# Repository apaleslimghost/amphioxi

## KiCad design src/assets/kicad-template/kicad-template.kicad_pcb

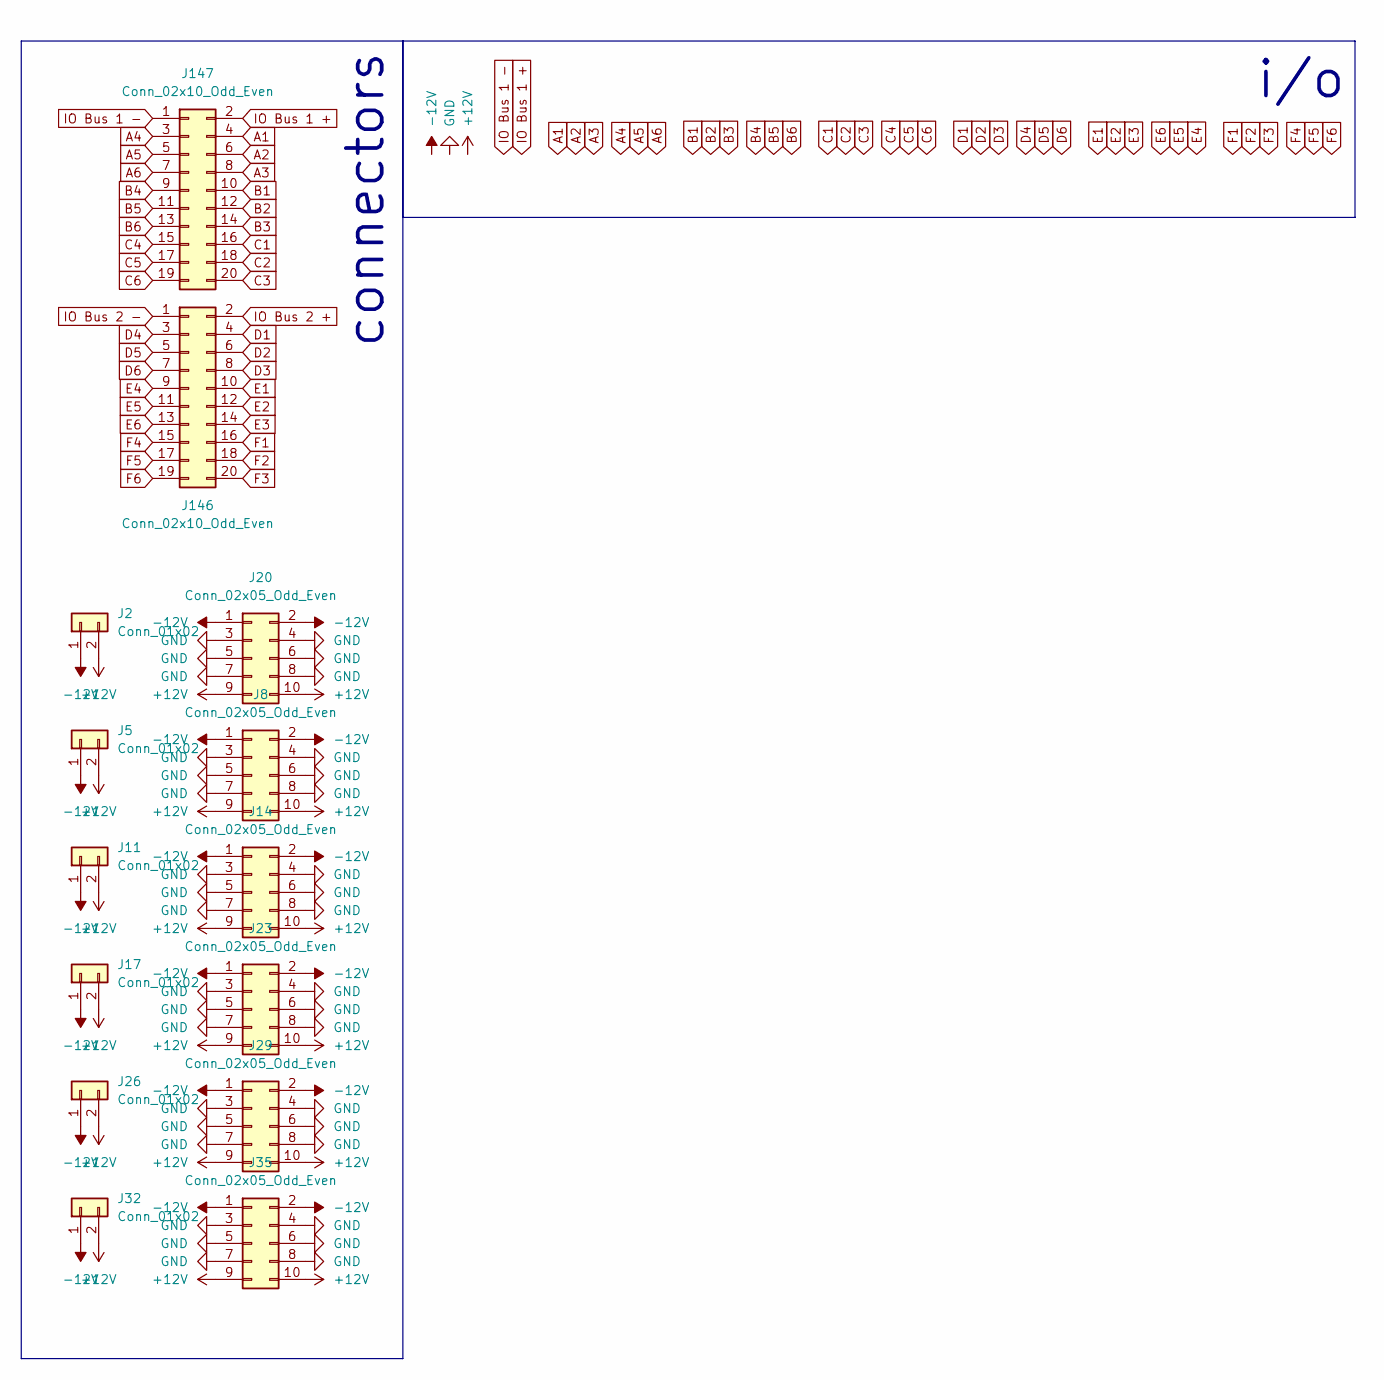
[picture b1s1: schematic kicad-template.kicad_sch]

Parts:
J2, J5, J11, J17, J26, J32: Conn_01x02; PinHeader_1x02_P2.54mm_Vertical_StripboardEuroPower
J8, J14, J20, J23, J29, J35: Conn_02x05_Odd_Even; PinHeader_2x05_P2.54mm_Vertical_StripboardEuroPower
J146, J147: Conn_02x10_Odd_Even; PinHeader_2x10_P2.00mm_Vertical

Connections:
+12V: J2.2, J5.2, J8.9, J8.10, J11.2, J14.9, J14.10, J17.2, J20.9, J20.10, J23.9, J23.10, J26.2, J29.9, J29.10, J32.2, J35.9, J35.10
-12V: J2.1, J5.1, J8.1, J8.2, J11.1, J14.1, J14.2, J17.1, J20.1, J20.2, J23.1, J23.2, J26.1, J29.1, J29.2, J32.1, J35.1, J35.2
A1: J147.4
A2: J147.6
A3: J147.8
A4: J147.3
A5: J147.5
A6: J147.7
B1: J147.10
B2: J147.12
B3: J147.14
B4: J147.9
B5: J147.11
B6: J147.13
C1: J147.16
C2: J147.18
C3: J147.20
C4: J147.15
C5: J147.17
C6: J147.19
D1: J146.4
D2: J146.6
D3: J146.8
D4: J146.3
D5: J146.5
D6: J146.7
E1: J146.10
E2: J146.12
E3: J146.14
E4: J146.9
E5: J146.11
E6: J146.13
F1: J146.16
F2: J146.18
F3: J146.20
F4: J146.15
F5: J146.17
F6: J146.19
GND: J8.3, J8.4, J8.5, J8.6, J8.7, J8.8, J14.3, J14.4, J14.5, J14.6, J14.7, J14.8, J20.3, J20.4, J20.5, J20.6, J20.7, J20.8, J23.3, J23.4, J23.5, J23.6, J23.7, J23.8, J29.3, J29.4, J29.5, J29.6, J29.7, J29.8, J35.3, J35.4, J35.5, J35.6, J35.7, J35.8
IO Bus 1 +: J147.2
IO Bus 1 -: J147.1
IO Bus 2 +: J146.2
IO Bus 2 -: J146.1

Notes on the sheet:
i/o
connectors

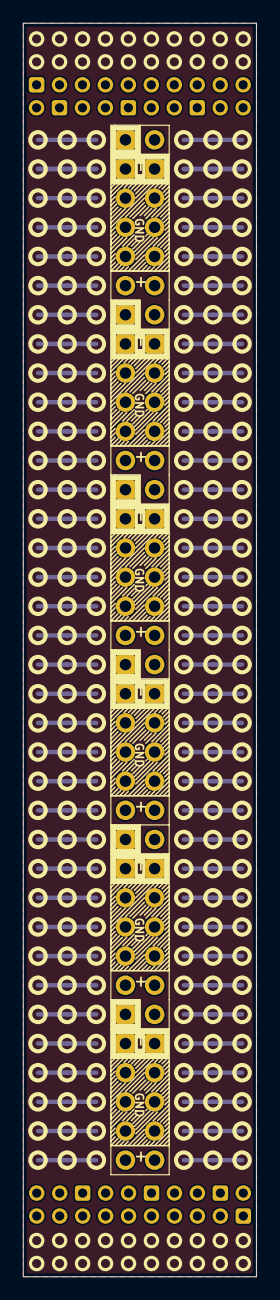
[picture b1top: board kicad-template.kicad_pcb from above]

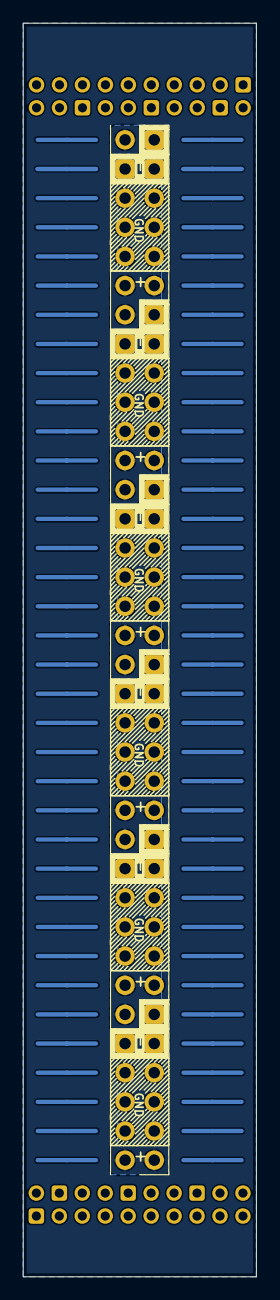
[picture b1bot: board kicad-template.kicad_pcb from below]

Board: 2 copper layers, 20.3 x 109.2 mm, 14 parts (2 on the bottom side), 3 nets.

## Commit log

2025-04-22 everything lol
2025-04-30 select and display components
2025-04-30 use zustand for state management and add localstorage
2025-04-30 remove comment
2025-04-30 clean up imports
2025-05-05 rudimentary pinout list
    (and a geographical pinout display that doesn't really work)
2025-05-05 deleting components
2025-05-05 allow selecting centre component after deleting left and right components
2025-12-31 add led
2025-12-31 add kicad template(?)
2025-12-31 add github action
2025-12-31 whatever
2025-12-31 vite base path
2025-12-31 wait this is amphioxi
